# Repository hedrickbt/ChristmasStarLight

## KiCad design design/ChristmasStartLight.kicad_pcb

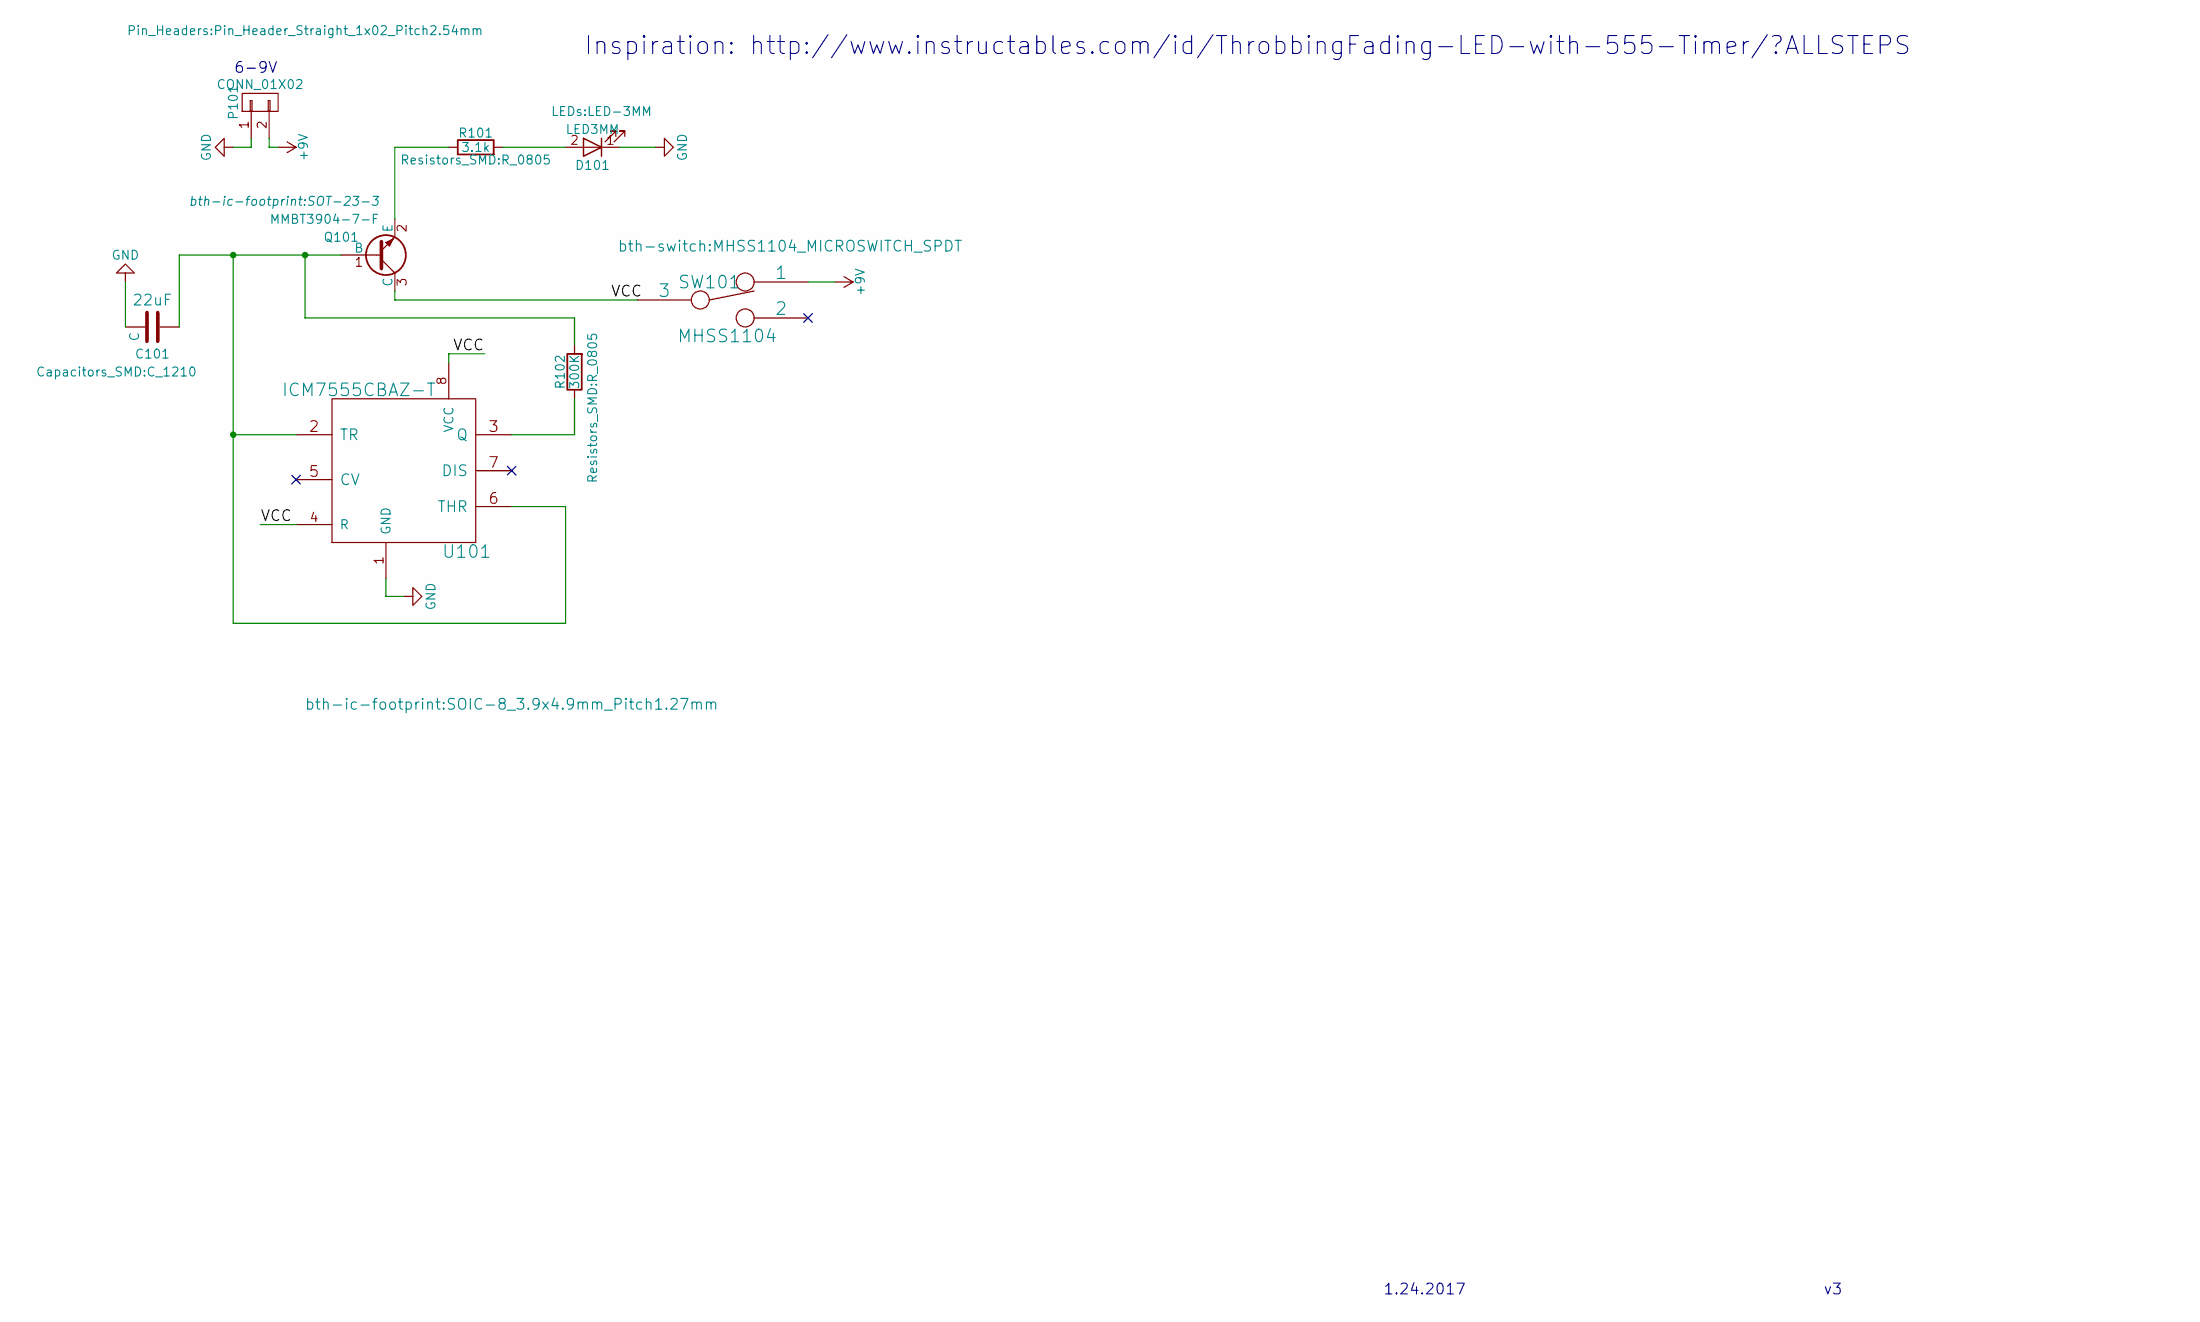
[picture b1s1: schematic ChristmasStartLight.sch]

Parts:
C101: C; C_1210
D101: LED3MM; LED-3MM
P101: CONN_01X02; Pin_Header_Straight_1x02_Pitch2.54mm
Q101: MMBT3904-7-F; SOT-23-3
R101: 3.1k; R_0805
R102: 300K; R_0805
SW101: MHSS1104; MHSS1104_MICROSWITCH_SPDT
U101: ICM7555CBAZ-T; SOIC-8_3.9x4.9mm_Pitch1.27mm

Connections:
+9V: P101.2, SW101.1
/VCC: Q101.3 (C), SW101.3, U101.4 (R), U101.8 (VCC)
GND: C101.2, D101.1 (K), P101.1, U101.1 (GND)
unnamed: C101.1, Q101.1 (B), R102.2, U101.2 (TR), U101.6 (THR)
unnamed: D101.2 (A), R101.2
unnamed: Q101.2 (E), R101.1
unnamed: R102.1, U101.3 (Q)

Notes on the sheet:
6-9V
Inspiration: http://www.instructables.com/id/ThrobbingFading-LED-with-555-Timer/?ALLSTEPS
1.24.2017

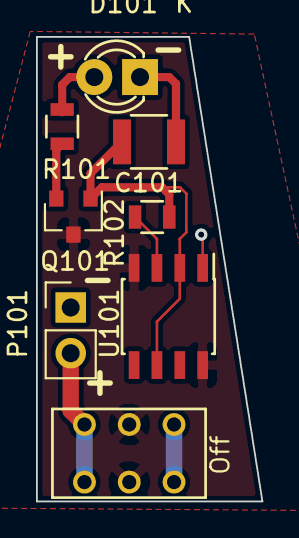
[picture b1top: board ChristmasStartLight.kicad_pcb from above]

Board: 2 copper layers, 12.5 x 25.8 mm, 8 parts (0 on the bottom side), 7 nets.

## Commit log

2013-09-11 Initial - still need to figure out battery mounting
2013-09-15 Parts and PCB done
2013-11-09 Added the gerbers
2013-11-17 ChristmasStarLight_v3
2017-01-09 some update
2017-01-09 rescued parts
2017-01-11 first smd version v2
2017-01-25 Started on v3 of the schematic. Still need to do PCB layout.
2017-01-25 Finished v3 fixes including layout and submitted to OshPark
2024-12-17 Misc changes
